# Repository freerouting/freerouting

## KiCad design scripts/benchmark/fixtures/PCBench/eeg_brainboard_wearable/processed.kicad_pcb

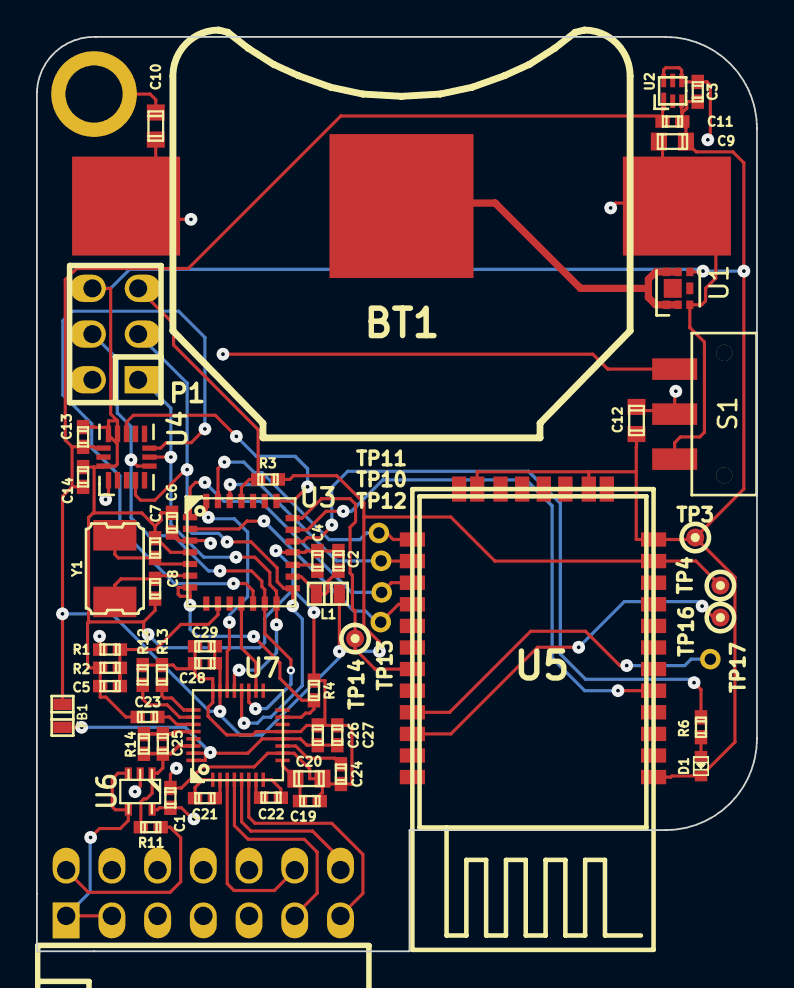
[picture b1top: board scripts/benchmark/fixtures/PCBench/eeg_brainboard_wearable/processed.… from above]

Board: 4 copper layers, 40.0 x 50.8 mm, 59 parts (0 on the bottom side), 48 nets.

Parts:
BT1: LIR2450; keystone_3008
C1, C2, C4, C5, C6, C13, C14, C19, C27, C29: 0.1uF; c_0402
C3, C11, C23, C24, C26, C28: 1uF; c_0402
C7, C8: 30pF; c_0402
C9, C10, C12, C20: 10uF; c_0603
C21, C22: 4.7nF; c_0402
C25: 1.5nF; c_0402
D1: RED; Led_0402
FB1: BLM18PG121SN1; inductor_smd_0603
L1: 10uH; inductor_smd_0603
MTG1: MHOLE; mounting_hole_0in125
P1: ICSP; pin_strip_3x2
P2: CONN_7X2; pin_socket_7x2-90
R1: 2.2M; r_0402
R2, R14: 1M; r_0402
R3, R4, R12, R13: 10k; r_0402
R6: 2.2k; r_0402
R11: 51k; r_0402
S1: JS102011SAQN
TP3: GND; testpoint_1mm
TP4: 3V3; testpoint_1mm
TP10: BTRX; PINTST
TP11: BTTX; PINTST
TP12: BTRTS; PINTST
TP13: BTCTS; PINTST
TP14: CONN; testpoint_1mm
TP16: FACT; testpoint_1mm
TP17: STATUS; PINTST
U1: FR015L3EZ; MLP6-2x2
U2: TPS727XXDSE; S-PWSON-N6
U3: ATMEGA328P-28PIN; qfn-28-nopad
U4: ADXL362; 16-LGA-3x3.25
U5: BLUETOOTH-RN42; roving_rn-42
U6: OPA376; sc70-5
U7: ADS1291/2; s-pvqfn-n32-nopad
Y1: ABM3B-8.000MHZ; crystal_smd_5x3.2mm

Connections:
+BATT: BT1.1, C9.1, C10.1, R1.1, S1.1, U1.3
/AREF: C4.1, U3.17
/AVCC: C2.1, L1.1, U3.16
/B-: BT1.2, U1.1, U1.2, U1.5, U1.6
/BATT_MON: C5.1, R1.2, R2.1, U3.9
/BT_CONN: TP14.1, U3.21, U5.19
/BT_RESET: U3.20, U5.5
/Electrode front-end/GPIO1: R12.1, U7.26
/Electrode front-end/GPIO2: R13.1, U7.25
/Electrode front-end/PGA1N: C21.2, U7.1
/Electrode front-end/PGA1P: C21.1, U7.2
/Electrode front-end/PGA2N: C22.2, U7.7
/Electrode front-end/PGA2P: C22.1, U7.8
/Electrode front-end/RLDIN: C25.1, R11.1, R14.1, U6.1, U7.29, U7.30
/Electrode front-end/RLDINV: C25.2, R14.2, U7.28
/Electrode front-end/VCAP1: C24.1, U7.11
/Electrode front-end/VCAP2: C23.1, U7.27
/Electrode front-end/VREFP: C19.1, C20.1, U7.9
/FACTORY_RESET: TP16.1, U5.22
/STATUS: TP17.1, U5.21
/USER_LED: R6.2, U3.19
/~MCU_CTS: TP12.1, U3.1, U5.15
/~MCU_RTS: TP13.1, U3.2, U5.16
AVDD: C1.1, C26.1, C27.1, FB1.2, U6.5, U7.12, U7.31, U7.32
CH1N: P2.12, U7.3
CH1P: P2.11, U7.4
CH2N: P2.14, U7.5
CH2P: P2.13, U7.6
DVDD: C6.1, C11.1, C13.1, C14.1, C28.1, C29.1, FB1.1, L1.2, R3.1, TP4.1, U2.1, U3.3, U4.1, U4.14, U5.11, U7.23
GND: C1.2, C2.2, C3.2, C4.2, C5.2, C6.2, C7.1, C8.1, C9.2, C10.2, C11.2, C12.2, C13.2, C14.2, C19.2, C20.2, C23.2, C24.2, C26.2, C27.2, C28.2, C29.2, D1.2, MTG1.1, P1.6, R2.2, R4.1, R12.2, R13.2, TP3.1, U1.4, U2.3, U3.4, U3.18, U4.12, U4.13, U4.16, U5.1, U5.12, U5.28, U5.29, U6.2, U7.10, U7.13, U7.24
INT1: U3.22, U4.11
MCU_RX: TP11.1, U3.26, U5.14
MCU_TX: TP10.1, U3.27, U5.13
MISO: P1.1, U3.14, U4.7, U7.21
MOSI: P1.4, U3.13, U4.6, U7.19
unnamed: D1.1, R6.1
unnamed: C8.2, U3.6, Y1.2
unnamed: C7.2, U3.5, Y1.1
RLD: P2.2, R11.2
SCLK: P1.3, U3.15, U4.4, U7.20
SHIELD: P2.1, P2.3, U6.3, U6.4
VCC: C3.1, C12.1, S1.2, U2.4, U2.6
VEXT: P1.2, S1.3
~AFE_CS: U3.11, U7.18
~AFE_DRDY: U3.28, U7.22
~AFE_PWDN: R4.2, U3.7, U7.15
~MCU_RESET: P1.5, R3.2, U3.25
~XL_CS: U3.12, U4.8

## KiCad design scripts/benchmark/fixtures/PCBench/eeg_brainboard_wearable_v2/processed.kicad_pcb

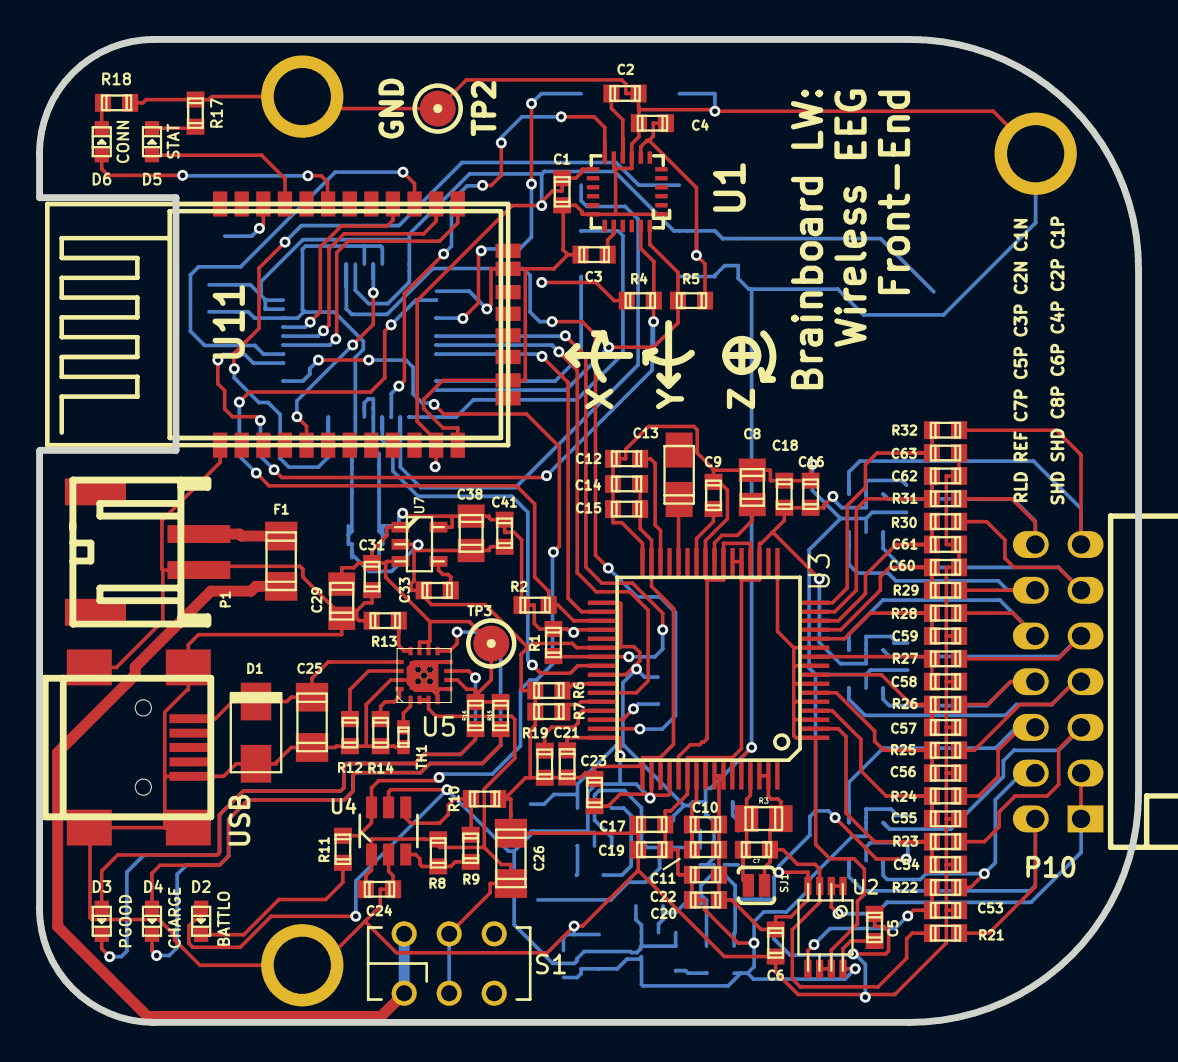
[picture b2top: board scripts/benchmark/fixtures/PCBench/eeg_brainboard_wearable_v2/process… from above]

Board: 4 copper layers, 61.1 x 54.6 mm, 134 parts (0 on the bottom side), 89 nets.

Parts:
C1, C2, C5, C6, C11, C15, C18, C19, C22, C23, C24, C31, C42, C43, C45, C47, C48, C49, C50, C51, C52: 0.1uF; c_0603
C3: 2.2nF; c_0603
C4, C33, C34, C35: 0.01uF; c_0603
C7: 1nF; c_0603
C8, C29, C36, C37, C38, C46: 10uF; c_0805
C9, C10, C12, C14, C16, C17, C20, C21, C27, C28, C30, C32: 1uF; c_0603
C13: 100uF; c_tant_S
C25: 2.2uF; c_1206
C26: 10uF; c_1206
C39, C40, C41, C44: 2.2uF; c_0603
C53, C54, C55, C56, C57, C58, C59, C60, C61, C62, C63: 4.7nF; c_0603
CON1: USB; USB_MINI_B
D1: SMAJ7.0A; do214ac
D2: BATTLO; Led_0603
D3: PGOOD; Led_0603
D4: CHARGE; Led_0603
D5: STAT; Led_0603
D6: CONN; Led_0603
F1: PTC 500mA; r_1206
MTG1, MTG2, MTG3: MHOLE; BBB_MHOLE
P1: JST; s2b-ph-sm4-tb
P8: CONN_5X2; bb02-hp10
P10: CONN_14; pin_socket_7x2-90
R1, R2: 10K; r_0603
R3: 499K,0.1%; r_0805
R4, R5: 4.7k; r_0603
R6, R7, R19, R20: 10k; r_0603
R8: 562k; r_0603
R9: 51.1k; r_0603
R10: 383k; r_0603
R11, R15, R16, R17, R18: 2.2k; r_0603
R12: 52.3k; r_0603
R13: 1.18k; r_0603
R14: 4.42k; r_0603
R21, R22, R23, R24, R25, R26, R27, R28, R29, R30, R31, R32: 4.99K; r_0603
S1: DPDT; JS202011AQN
SJ1: NO BIAS FILT; SparkFun-Passives-SJ_2S-NO
TH1: NTC 10K; r_0402
TP1, TP2: GND; testpoint_2mm
TP3: PREREG; testpoint_2mm
TP4: -3V3; testpoint_2mm
TP5: +2V5; testpoint_2mm
TP6: -2V5; testpoint_2mm
TP7: BTRST; testpoint_2mm
TP8: 3V3; testpoint_2mm
U1: MPU6050; QFN24-4x4
U2: OPA2376; msoic-8
U3: ADS1299; TQFP_64
U4: LTC1998; tsot23-6
U5: BQ24074(T); s-pvqfn-n16-vias
U6: TPS60403; sot23-5
U7: TPS73233; sot23-5
U8: TPS73225; sot23-5
U9: TPS72325; sot23-5
U10: ATUC3L064; -TQFP48
U11: BLUETOOTH-RN42; roving_rn-42
U12, U13, U14: TPD4E001DBV; sot23-6

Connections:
+2.5V: C5.1, C16.1, C17.1, C18.1, C19.1, C20.1, C22.1, C36.1, C39.1, C42.1, C50.1, C51.1, C52.1, TP5.1, U2.8, U3.19, U3.21, U3.22, U3.54, U3.56, U3.59, U8.5, U12.5, U13.5, U14.5
+3.3V: C1.1, C4.1, C21.1, C23.1, C27.1, C32.1, C38.1, C41.1, C43.1, C44.1, C45.1, C46.1, C47.1, C48.1, C49.1, D2.1, P8.4, R1.1, R2.1, R4.1, R5.1, TP8.1, U1.8, U1.13, U3.36, U3.48, U3.50, U3.52, U4.5, U6.2, U7.5, U8.1, U8.3, U10.17, U10.18, U10.34, U10.35, U10.42, U10.48, U11.11
+BATT: C24.1, C26.1, R8.1, S1.2, S1.5, U4.1, U5.2, U5.3
-2.5V: C6.1, C8.1, C9.2, C10.2, C11.2, C12.2, C13.2, C14.1, C15.1, C16.2, C18.2, C20.2, C22.2, C37.1, C40.1, C42.2, C50.2, C51.2, C52.2, TP6.1, U2.4, U3.20, U3.23, U3.25, U3.32, U3.53, U3.57, U3.58, U9.5, U12.2, U13.2, U14.2
-3.3V: C30.1, TP4.1, U6.1, U9.2, U9.3
/BATTLO: R11.1, U4.6, U10.26
/Brainboard AFE/BIASINV: C7.1, R3.2, SJ1.1, U3.61
/Brainboard AFE/SRB1: U2.6, U2.7, U3.1, U3.3, U3.5, U3.7, U3.9, U3.11, U3.17
/Brainboard AFE/VCAP1: C13.1, U3.28
/Brainboard AFE/VCAP2: C12.1, U3.30
/Brainboard AFE/VCAP3: C10.1, C11.1, U3.55
/Brainboard AFE/VCAP4: C9.1, U3.26
/Brainboard AFE/VREFP: C8.2, U3.24
/Brainboard Analog In/BIAS_ELEC: P10.2, R21.1, U14.3
/Brainboard Analog In/CH1ELEC_N: P10.14, R31.1, U12.6
/Brainboard Analog In/CH1ELEC_P: P10.13, R32.1, U12.4
/Brainboard Analog In/CH2ELEC_N: P10.12, R29.1, U12.3
/Brainboard Analog In/CH2ELEC_P: P10.11, R30.1, U12.1
/Brainboard Analog In/CH3ELEC_P: P10.10, R28.1, U13.4
/Brainboard Analog In/CH4ELEC_P: P10.9, R27.1, U13.6
/Brainboard Analog In/CH5ELEC_P: P10.8, R26.1, U13.1
/Brainboard Analog In/CH6ELEC_P: P10.7, R25.1, U13.3
/Brainboard Analog In/CH7ELEC_P: P10.6, R24.1, U14.4
/Brainboard Analog In/CH8ELEC_P: P10.5, R23.1, U14.6
/Brainboard Analog In/REF_ELEC: P10.4, R22.1, U14.1
/Brainboard Bluetooth/FACTORY: TP7.1, U11.22
/Brainboard Bluetooth/STATUS: D6.1, U11.19
/Brainboard Bluetooth/STATUSn: D5.1, U11.21
/Brainboard IMU/CPOUT: C3.1, U1.20
/Brainboard IMU/REGOUT: C2.1, U1.10
/Brainboard MCU/RESET_MCU: P8.6, U10.22
/Brainboard MCU/TCK: P8.1, U10.11
/Brainboard MCU/TDI: P8.9, U10.4
/Brainboard MCU/TDO: P8.3, U10.13
/Brainboard MCU/TMS: P8.5, U10.14
/Brainboard Power/B+: F1.2, P1.1
/Brainboard Power/ILIM: R13.1, U5.12
/Brainboard Power/ISET: R14.1, U5.16
/Brainboard Power/OUT: C29.1, C31.1, R15.1, R16.1, TP3.1, U5.6, U5.10, U5.11, U7.1, U7.3
/Brainboard Power/TMR: R12.1, U5.14
/Brainboard Power/TS: TH1.1, U5.1
/Brainboard Power/VBUS: C25.1, CON1.1, D1.2, U5.13
/Brainboard Power/_B+: F1.1, S1.1, S1.4
/Brainboard Power/~CHG: D4.2, U5.9
/Brainboard Power/~PGOOD: D3.2, U5.7
/CS: R1.2, U3.39, U10.6
/DRDY: U3.47, U10.41
/PWDN: R2.2, U3.35, U10.2
AGND: C1.2, C2.2, C3.2, C4.2, C5.2, C6.2, C14.2, C15.2, C17.2, C19.2, C21.2, C23.2, C24.2, C25.2, C26.2, C27.2, C29.2, C30.2, C31.2, C32.2, C33.2, C34.2, C35.2, C36.2, C37.2, C38.2, C39.2, C40.2, C41.2, C43.2, C44.2, C45.2, C46.2, C47.2, C48.2, C49.2, C53.2, C54.2, C55.2, C56.2, C57.2, C58.2, C59.2, C60.2, C61.2, C62.2, C63.2, CON1.5, CON1.6, CON1.7, CON1.8, CON1.9, D1.1, MTG1.1, MTG2.1, MTG3.1, P1.2, P8.2, P8.10, R6.2, R7.2, R10.2, R12.2, R13.2, R14.2, R17.2, R18.2, R19.2, R20.2, TH1.2, TP1.1, TP2.1, U1.1, U1.9, U1.11, U1.18, U3.31, U3.33, U3.38, U3.41, U3.49, U3.51, U3.60, U4.2, U5.4, U5.5, U5.8, U5.15, U5.17, U6.4, U7.2, U8.2, U9.1, U10.1, U10.19, U10.33, U10.43, U10.45, U11.1, U11.12, U11.28, U11.29
AIN1N: C62.1, R31.2, U3.15
AIN1P: C63.1, R32.2, U3.16
AIN2N: C60.1, R29.2, U3.13
AIN2P: C61.1, R30.2, U3.14
AIN3P: C59.1, R28.2, U3.12
AIN4P: C58.1, R27.2, U3.10
AIN5P: C57.1, R26.2, U3.8
AIN6P: C56.1, R25.2, U3.6
AIN7P: C55.1, R24.2, U3.4
AIN8P: C54.1, R23.2, U3.2
BIAS: C7.2, R3.1, R21.2, SJ1.2, U2.3, U3.62, U3.63
IMU_INT: U1.12, U10.15
MISO: U3.43, U10.7
MOSI: U3.34, U10.8
unnamed: R20.1, U3.46
unnamed: R19.1, U3.45
unnamed: R7.1, U3.44
unnamed: R6.1, U3.42
unnamed: C33.1, U7.4
unnamed: D3.1, R16.2
unnamed: D4.1, R15.2
unnamed: R9.2, R10.1, U4.4
unnamed: R8.2, R9.1, U4.3
unnamed: D2.2, R11.2
unnamed: C28.2, U6.3
unnamed: C28.1, U6.5
unnamed: C34.1, U8.4
unnamed: C35.1, U9.4
unnamed: D6.2, R18.1
unnamed: D5.2, R17.1
REF_IN: C53.1, R22.2, U2.5
RESET_BT: U10.44, U11.5
SCL: R4.2, U1.23, U10.28
SCLK: U3.40, U10.16
SDA: R5.2, U1.24, U10.12
SHIELD: P10.1, P10.3, U2.1, U2.2
UARTBT_CTS: U10.29, U11.15
UARTBT_RTS: U10.32, U11.16
UARTBT_RX: U10.31, U11.14
UARTBT_TX: U10.30, U11.13

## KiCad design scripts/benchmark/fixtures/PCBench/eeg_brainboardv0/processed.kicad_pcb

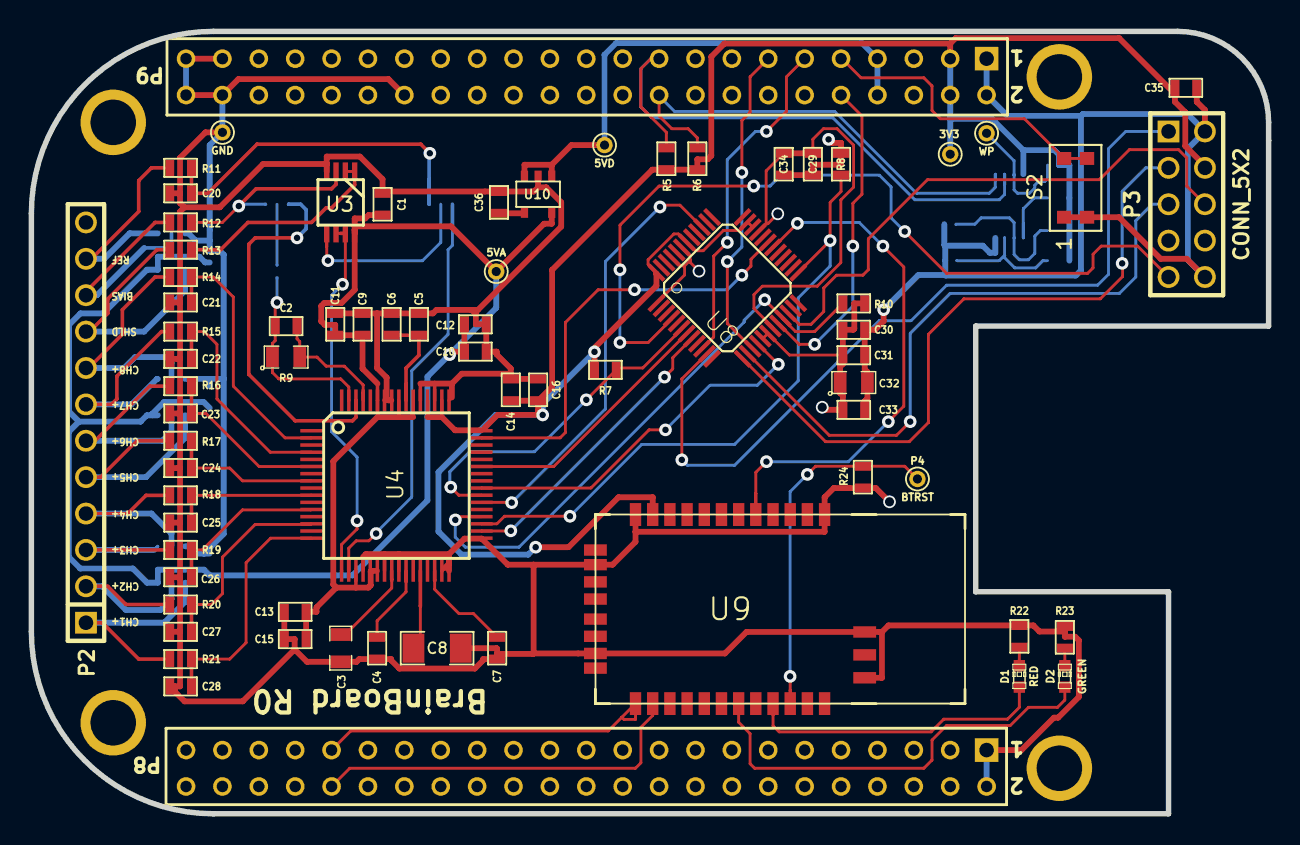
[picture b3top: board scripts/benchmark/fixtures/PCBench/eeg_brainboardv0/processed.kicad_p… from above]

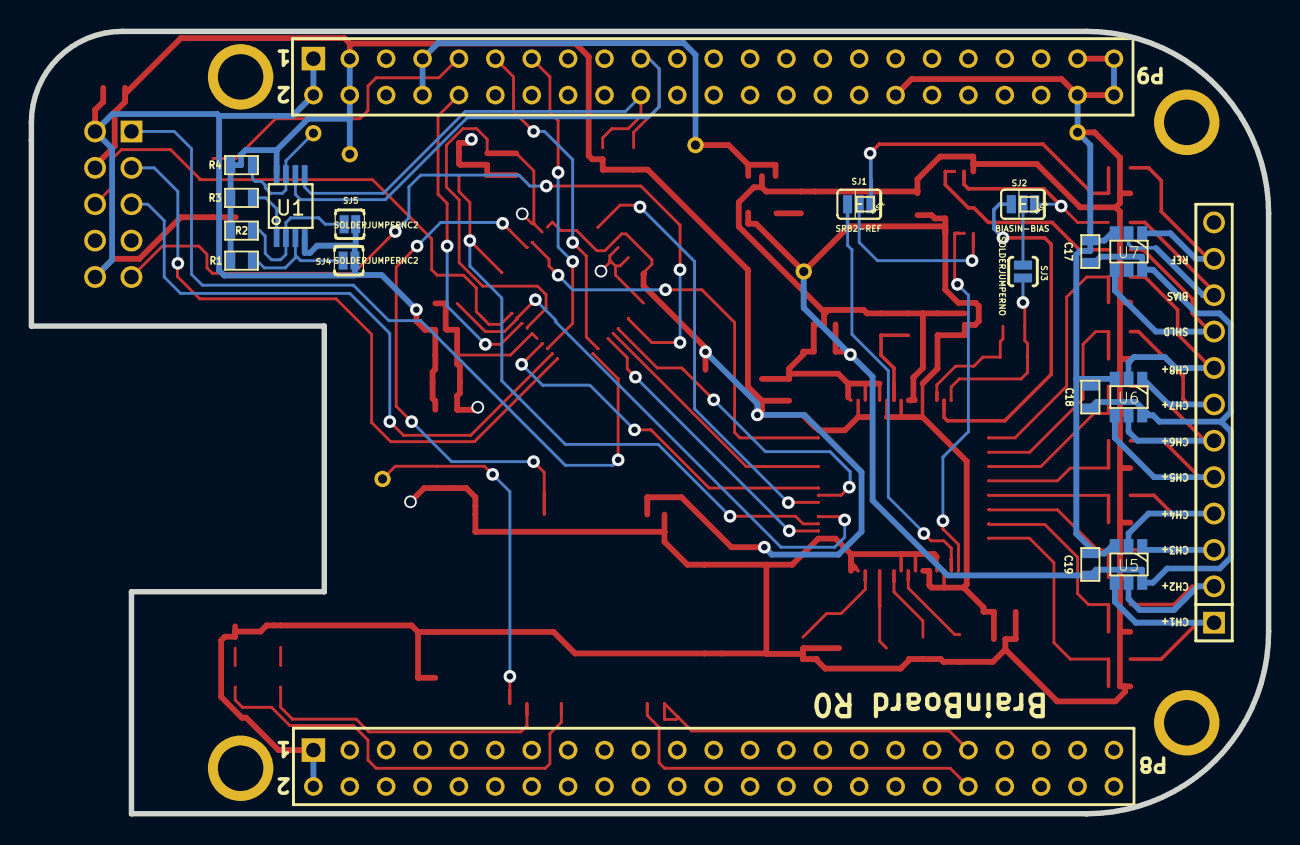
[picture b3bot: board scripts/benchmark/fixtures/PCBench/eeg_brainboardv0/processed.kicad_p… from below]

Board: 4 copper layers, 86.4 x 54.6 mm, 86 parts (16 on the bottom side), 70 nets.

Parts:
C1, C6, C11, C12, C15, C16, C17, C18, C19, C29, C31, C33, C34, C35, C36: 0.1uF; SM0603
C2: 1nF; SM0603
C3, C32: 10uF; SM0805
C4, C5, C7, C9, C10, C13, C14: 1uF; SM0603
C8: 100uF; SM1206
C20, C21, C22, C23, C24, C25, C26, C27, C28: 4.7nF; SM0603
C30: 2.2uF; SM0603
D1: RED; LED-0603
D2: GREEN; LED-0603
P1: WP; PINTST
P2: CONN_12; PIN_ARRAY-12X1
P3: CONN_5X2; PIN_ARRAY_5x2
P4: BTRST; PINTST
P5: GND; PINTST
P6: 5VD; PINTST
P7: 3V3; PINTST
P8: 5VA; PINTST
R1, R2, R3: 4.7K; SM0603
R4, R7, R8, R10, R24: 10K; SM0603
R5, R6: 5.6K; SM0603
R9: 499K,0.1%; SM0805
R11, R12, R13, R14, R15, R16, R17, R18, R19, R20, R21: 4.99K; SM0603
R22, R23: 330; SM0603
S2: SMT_BUTTON; KMR231GLFS
SJ1, SJ2: SOLDERJUMPER_2WAYPASTE2&3; SparkFun-Passives-SJ_3_PASTE2&3
SJ3: SOLDERJUMPERNO; SparkFun-Passives-SJ_2S-NO
SJ4, SJ5: SOLDERJUMPERNC2; SparkFun-Passives-SJ_2S-NOTRACE
U1: 24C256; SSOP8
U2: BEAGLEBONE_BLACK
U3: OPA2376; MSOP_8
U4: ADS1299; TQFP_64
U5, U6, U7: TPD4E001; SOT23_6
U8: ATUC3L064; -TQFP48
U9: BLUETOOTH-RN42; SparkFun-RF-RN41
U10: TPS73150; SOT23-5

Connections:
3V3: C14.1, C16.1, C29.1, C30.1, C31.1, C32.1, C33.1, C34.1, C35.1, P3.4, P7.1, R1.1, R2.1, R3.1, R4.1, R5.1, R6.1, R7.1, R8.1, R10.1, U1.8, U2.B3, U2.B4, U4.48, U4.50, U4.52, U8.17, U8.18, U8.34, U8.35, U8.42, U8.48, U9.11
+5VA: C1.1, C9.1, C10.1, C11.1, C12.1, C13.1, C15.1, C17.1, C18.1, C19.1, P8.1, U3.8, U4.19, U4.21, U4.22, U4.54, U4.56, U4.59, U5.6, U6.6, U7.6, U10.5
+5VD: P6.1, U2.B7, U2.B8, U10.1, U10.3
/A0: R3.2, U1.1
/A1: R2.2, SJ5.1, U1.2
/A2: R1.2, SJ4.1, U1.3
/BrainBoard AFE/BIASIN: SJ2.1, U4.62
/BrainBoard AFE/BIASINV: C2.1, R9.2, U4.61
/BrainBoard AFE/BIASOUT: C2.2, R9.1, SJ3.2, U4.63
/BrainBoard AFE/SRB1: U3.6, U3.7, U4.17
/BrainBoard AFE/SRB2: SJ1.1, U4.18
/BrainBoard AFE/VCAP1: C8.1, U4.28
/BrainBoard AFE/VCAP2: C7.1, U4.30
/BrainBoard AFE/VCAP3: C5.1, C6.1, U4.55
/BrainBoard AFE/VCAP4: C4.1, U4.26
/BrainBoard AFE/VREFP: C3.2, U4.24
/BrainBoard Analog In/BIAS_ELEC: P2.10, R12.1, U7.2
/BrainBoard Analog In/BIAS_SHD: P2.9, R13.1, U7.4
/BrainBoard Analog In/CH1ELEC_P: P2.1, R21.1, U5.4
/BrainBoard Analog In/CH2ELEC_P: P2.2, R20.1, U5.5
/BrainBoard Analog In/CH3ELEC_P: P2.3, R19.1, U5.1
/BrainBoard Analog In/CH4ELEC_P: P2.4, R18.1, U5.2
/BrainBoard Analog In/CH5ELEC_P: P2.5, R17.1, U6.4
/BrainBoard Analog In/CH6ELEC_P: P2.6, R16.1, U6.5
/BrainBoard Analog In/CH7ELEC_P: P2.7, R15.1, U6.1
/BrainBoard Analog In/CH8ELEC_P: P2.8, R14.1, U6.2
/BrainBoard Analog In/REF_ELEC: P2.11, R11.1, U7.1
/BrainBoard Bluetooth/FACTORY: P4.1, R24.1, U9.22
/BrainBoard Bluetooth/STATUS: D2.1, U9.19
/BrainBoard Bluetooth/STATUSn: D1.1, U9.21
/BrainBoard MCU/RESET_MCU: P3.6, U8.22
/BrainBoard MCU/TCK: P3.1, U8.11
/BrainBoard MCU/TDI: P3.9, U8.4
/BrainBoard MCU/TDO: P3.3, U8.13
/BrainBoard MCU/TMS: P3.5, U8.14
/CS: R7.2, U4.39, U8.6
/DRDY: U4.47, U8.31
/PWDN: R8.2, U4.35, U8.25
/RESET: R10.2, U4.36, U8.21
/SCL: R5.2, U1.6, U2.B19
/SDA: R6.2, U1.5, U2.B20
/WP: P1.1, R4.2, U1.7
AGND: C1.2, C3.1, C4.2, C5.2, C6.2, C7.2, C8.2, C9.2, C10.2, C11.2, C12.2, C13.2, C14.2, C15.2, C16.2, C17.2, C18.2, C19.2, C20.2, C21.2, C22.2, C23.2, C24.2, C25.2, C26.2, C27.2, C28.2, C29.2, C30.2, C31.2, C32.2, C33.2, C34.2, C35.2, C36.2, P3.2, P3.10, P5.1, R22.2, R23.2, R24.2, S2.1, S2.3, SJ4.2, SJ5.2, U1.4, U2.A1, U2.A2, U2.B1, U2.B2, U2.B34, U2.B43, U2.B44, U2.B45, U2.B46, U3.4, U4.20, U4.23, U4.25, U4.31, U4.32, U4.33, U4.49, U4.51, U4.53, U4.57, U4.58, U5.3, U6.3, U7.3, U8.1, U8.19, U8.33, U8.43, U8.45, U9.1, U9.12, U9.25, U9.27, U9.28, U9.29, U10.2
AIN1P: C28.1, R21.2, U4.16
AIN2P: C27.1, R20.2, U4.14
AIN3P: C26.1, R19.2, U4.12
AIN4P: C25.1, R18.2, U4.10
AIN5P: C24.1, R17.2, U4.8
AIN6P: C23.1, R16.2, U4.6
AIN7P: C22.1, R15.2, U4.4
AIN8P: C21.1, R14.2, U4.2
BIAS: R12.2, SJ2.3, U3.3
MISO: U4.43, U8.7
MOSI: U4.34, U8.8
unnamed: S2.2, S2.4, U2.B9
unnamed: SJ2.2, SJ3.1
unnamed: SJ1.2, U3.5
unnamed: D2.2, R23.1
unnamed: D1.2, R22.1
unnamed: C36.1, U10.4
REF: C20.1, R11.2, SJ1.3
RESET_BT: U8.30, U9.5
SCLK: U4.40, U8.16
SHIELD: R13.2, U3.1, U3.2
START: U4.38, U8.39
SYS_RESETn: U2.B10, U8.20
UARTBT_RX: U2.A37, U9.13
UARTBT_TX: U2.A38, U9.14
UARTUC_RX: U2.B13, U8.15
UARTUC_TX: U2.B11, U8.10
